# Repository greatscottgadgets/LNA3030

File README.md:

# LNA3030

LNA3030 is an in-line SMA Low Noise Amplifier with SAW filter.

## hardware notes

Schematic and layout files were designed in KiCad, an open source electronic
design automation package.

This design may be assembled with any SAW filter with a standard 3.0 x 3.0 mm
footprint (DCC6C).

The PCB is designed to fit the Crystek SMA-KIT-1.5MF housing.

```
order of copper layers:
    Copper 1:  F (front)
    Copper 2:  In1
    Copper 3:  In2
    Copper 4:  B (back)

PCB description: 4 layer PCB 0.8 mm
    Copper       1:  0.035 mm (1 oz)
    Dielectric 1-2:  0.2 mm prepreg
    Copper       2:  0.0175 mm (0.5 oz)
    Dielectric 2-3:  0.265 mm core
    Copper       3:  0.0175 mm (0.5 oz)
    Dielectric 3-4:  0.2 mm prepreg
    Copper       4:  0.035 mm (1 oz)

7628 prepreg with Er=4.6
double side solder mask green
double side silkscreen white
7 mil minimum trace width
5 mil minimum isolation
```

PCBs of this specification are available from JLCPCB (JLC7628 4-layer 0.8 mm stackup).

## frequency options

LNA3030 may be populated with different components to support various frequency
bands.

frequency band | U4 part number       | L1-L4 part number | C1-C6 part number
---------------|----------------------|-------------------|-------------------
314-315 MHz    | B39321B3722U410      | HK1005R27J-T      | GCM1555C1H681JA16D
430-435 MHz    | B39431B3710U410      | HK1005R27J-T      | GCM155R71H471KA37D
868-870 MHz    | SF2415E              | HK1005R10J-T      | GCM1555C1H470JA16D

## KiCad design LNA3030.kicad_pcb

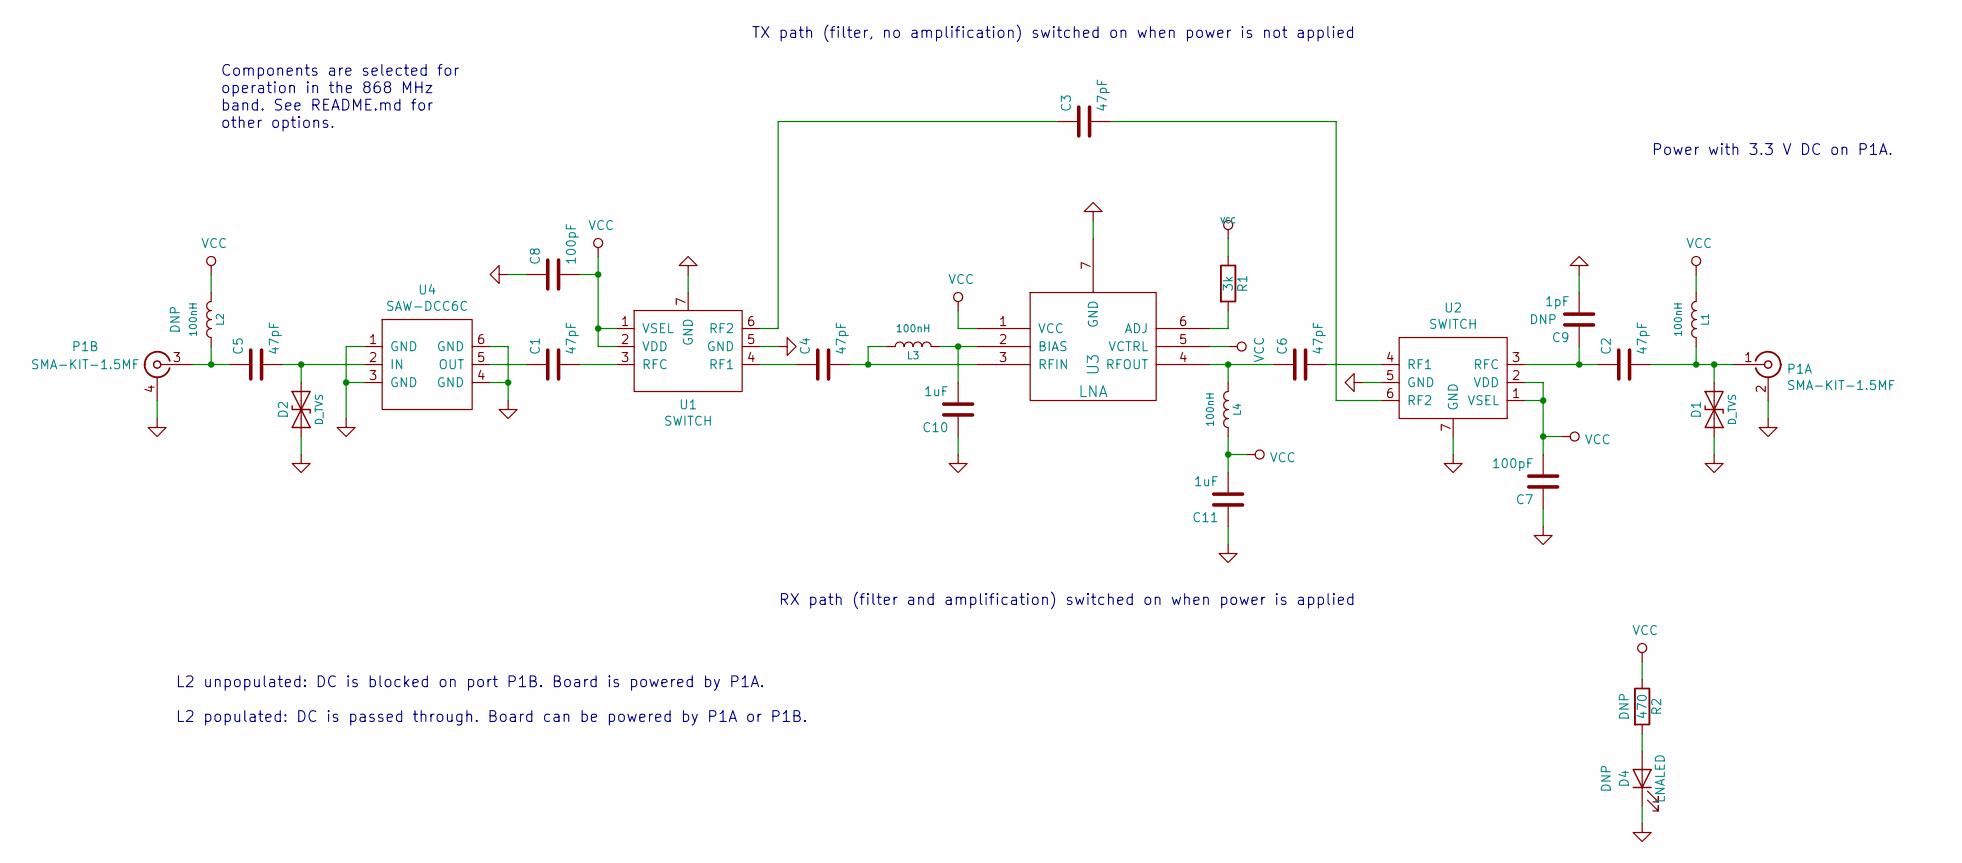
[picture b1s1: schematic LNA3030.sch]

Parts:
C1, C2, C3, C4, C5, C6: 47pF; 0402; Part Number GCM1555C1H470JA16D
C7, C8: 100pF; 0402; Part Number GCM1555C1H101JA16D
C9: 1pF; 0402
C10, C11: 1uF; 0402; Part Number LMK105BJ105KV-F
D1, D2: D_TVS; 0402; Part Number LXES15AAA1-153
D4: LNALED; 0402
L1, L2, L3, L4: 100nH; 0402; Part Number HK1005R10J-T
P1: SMA-KIT-1.5MF; Part Number SMA-KIT-1.5MF
R1: 3k; 0402; Part Number RMCF0402FT3K00
R2: 470; 0402; Part Number RMCF0402JT470R
U1, U2: SWITCH; GRF6011; Part Number GRF6011
U3: LNA; TSLP-7-1; Part Number BGB 741L7ESD E6327
U4: SAW-DCC6C; DCC6C; Part Number SF2415E

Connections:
GND: C7.1, C8.1, C9.2, C10.1, C11.1, D1.1 (A1), D2.1 (A1), D4.1 (K), P1.2 (SHIELD), P1.4 (SHIELD), U1.5 (GND), U1.7 (GND), U2.5 (GND), U2.7 (GND), U3.7 (GND), U4.1 (GND), U4.3 (GND), U4.4 (GND), U4.6 (GND)
unnamed: C1.1, U4.5 (OUT)
unnamed: C1.2, U1.3 (RFC)
unnamed: C2.1, C9.1, U2.3 (RFC)
unnamed: C2.2, D1.2 (A2), L1.1, P1.1 (RF)
unnamed: C3.1, U1.6 (RF2)
unnamed: C3.2, U2.6 (RF2)
unnamed: C4.1, U1.4 (RF1)
unnamed: C4.2, L3.1, U3.3 (RFIN)
unnamed: C5.1, L2.1, P1.3 (RF)
unnamed: C5.2, D2.2 (A2), U4.2 (IN)
unnamed: C6.1, L4.2, U3.4 (RFOUT)
unnamed: C6.2, U2.4 (RF1)
unnamed: C10.2, L3.2, U3.2 (BIAS)
unnamed: D4.2 (A), R2.2
unnamed: R1.2, U3.6 (ADJ)
VCC: C7.2, C8.2, C11.2, L1.2, L2.2, L4.1, R1.1, R2.1, U1.1 (VSEL), U1.2 (VDD), U2.1 (VSEL), U2.2 (VDD), U3.1 (VCC), U3.5 (VCTRL)

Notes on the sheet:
TX path (filter, no amplification) switched on when power is not applied
RX path (filter and amplification) switched on when power is applied
L2 unpopulated: DC is blocked on port P1B. Board is powered by P1A. L2 populated: DC is passed through. Board can be powered by P1A or P1B.
Components are selected for operation in the 868 MHz band. See README.md for other options.
Power with 3.3 V DC on P1A.

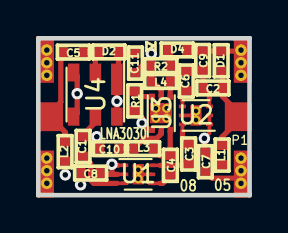
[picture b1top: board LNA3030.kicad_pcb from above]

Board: 4 copper layers, 11.7 x 8.7 mm, 25 parts (0 on the bottom side), 17 nets.

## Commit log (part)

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2020-08-05 initial commit, copied from LNA1109
2020-08-06 modify for DCC6C SAW filters
2020-08-06 correct C7 and C8 part selection
2020-08-16 disable gerber advanced attributes

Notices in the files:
LNA3030.kicad_pcb:
Copyright (c) 2014-2020 Great Scott Gadgets
Licensed under the CERN-OHL-P v2
